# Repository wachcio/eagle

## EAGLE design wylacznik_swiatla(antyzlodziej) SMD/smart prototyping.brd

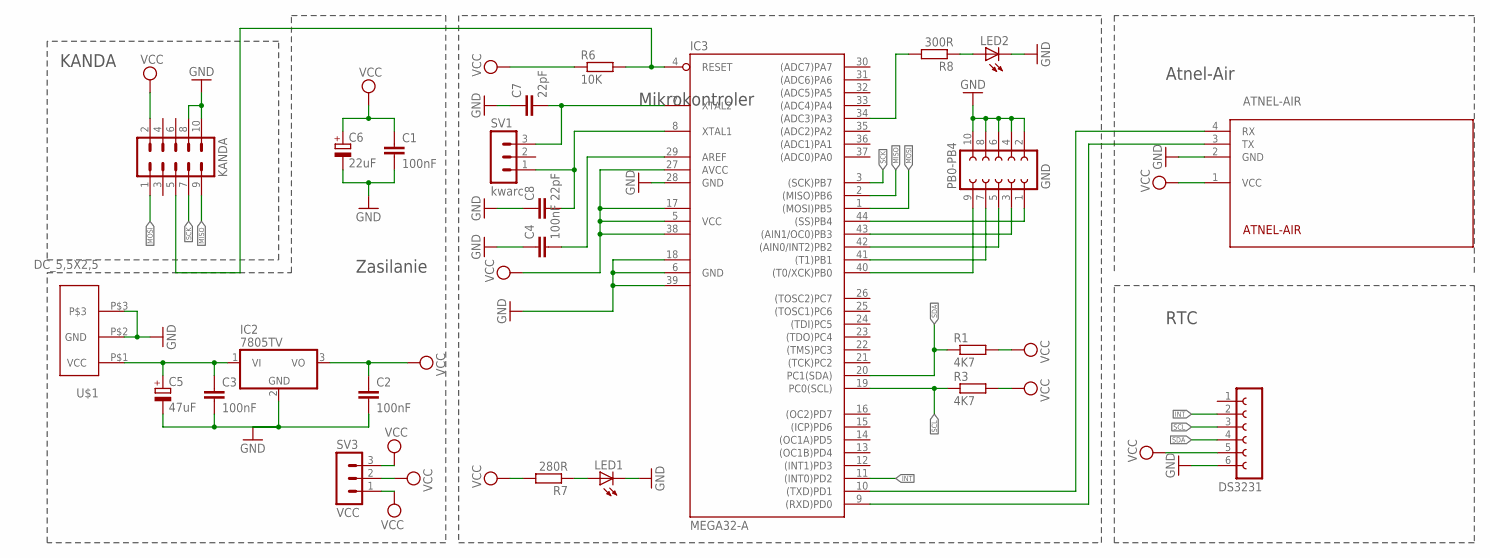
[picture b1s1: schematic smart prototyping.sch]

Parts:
ATNEL-AIR: ATNEL-AIR
C1, C2, C3, C4: 100nF; C025-024X044
C5: 47uF; B45181A
C6: 22uF; B45181A
C7, C8: 22pF; C025-024X044
DS3231: FE06-1; FE06
IC2: 7805TV; TO220V
IC3: MEGA32-A; TQFP44
KANDA: ML10
LED1, LED2: LED5MM
PB0-PB4: GND; FE05-2
R1, R3: 4K7; R1206W
R6: 10K; R1206W
R7: 280R; R1206W
R8: 300R; R1206W
SV1: kwarc; MA03-1
SV3: VCC; MA03-1
U$1: DC_5,5X2,5

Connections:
GND: ATNEL-AIR.2 (GND), C1.2, C2.2, C3.2, C4.1, C5.-, C6.-, C7.1, C8.1, DS3231.6, IC2.2 (GND), IC3.6 (GND), IC3.18 (GND1), IC3.28 (GND), IC3.39 (GND2), KANDA.8, KANDA.10, LED1.K (C), LED2.K (C), PB0-PB4.2, PB0-PB4.4, PB0-PB4.6, PB0-PB4.8, PB0-PB4.10, U$1.P$2 (GND), U$1.P$3
INT: DS3231.2, IC3.11 ((INT0)PD2)
MISO: IC3.2 ((MISO)PB6), KANDA.9
MOSI: IC3.1 ((MOSI)PB5), KANDA.1
unnamed: ATNEL-AIR.4 (RX), IC3.10 ((TXD)PD1)
unnamed: ATNEL-AIR.3 (TX), IC3.9 ((RXD)PD0)
unnamed: C4.2, IC3.29 (AREF)
unnamed: IC3.44 ((SS)PB4), PB0-PB4.1
unnamed: IC3.43 ((AIN1/OC0)PB3), PB0-PB4.3
unnamed: C3.1, C5.+, IC2.1 (VI), U$1.P$1 (VCC)
unnamed: IC3.42 ((AIN0/INT2)PB2), PB0-PB4.5
unnamed: IC3.41 ((T1)PB1), PB0-PB4.7
unnamed: IC3.40 ((T0/XCK)PB0), PB0-PB4.9
unnamed: C7.2, IC3.7 (XTAL2), SV1.3
unnamed: C8.2, IC3.8 (XTAL1), SV1.1
unnamed: LED1.A, R7.1
unnamed: LED2.A, R8.1
unnamed: IC3.34 ((ADC3)PA3), R8.2
RST: IC3.4 (RESET), KANDA.5, R6.2
SCK: IC3.3 ((SCK)PB7), KANDA.7
SCL: DS3231.3, IC3.19 (PC0(SCL)), R3.1
SDA: DS3231.4, IC3.20 (PC1(SDA)), R1.1
VCC: ATNEL-AIR.1 (VCC), C1.1, C2.1, C6.+, DS3231.5, IC2.3 (VO), IC3.5 (VCC), IC3.17 (VCC1), IC3.27 (AVCC), IC3.38 (VCC2), KANDA.2, R1.2, R3.2, R6.1, R7.2, SV3.1, SV3.2, SV3.3

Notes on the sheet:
Atnel-Air
KANDA
RTC
Zasilanie
Mikrokontroler

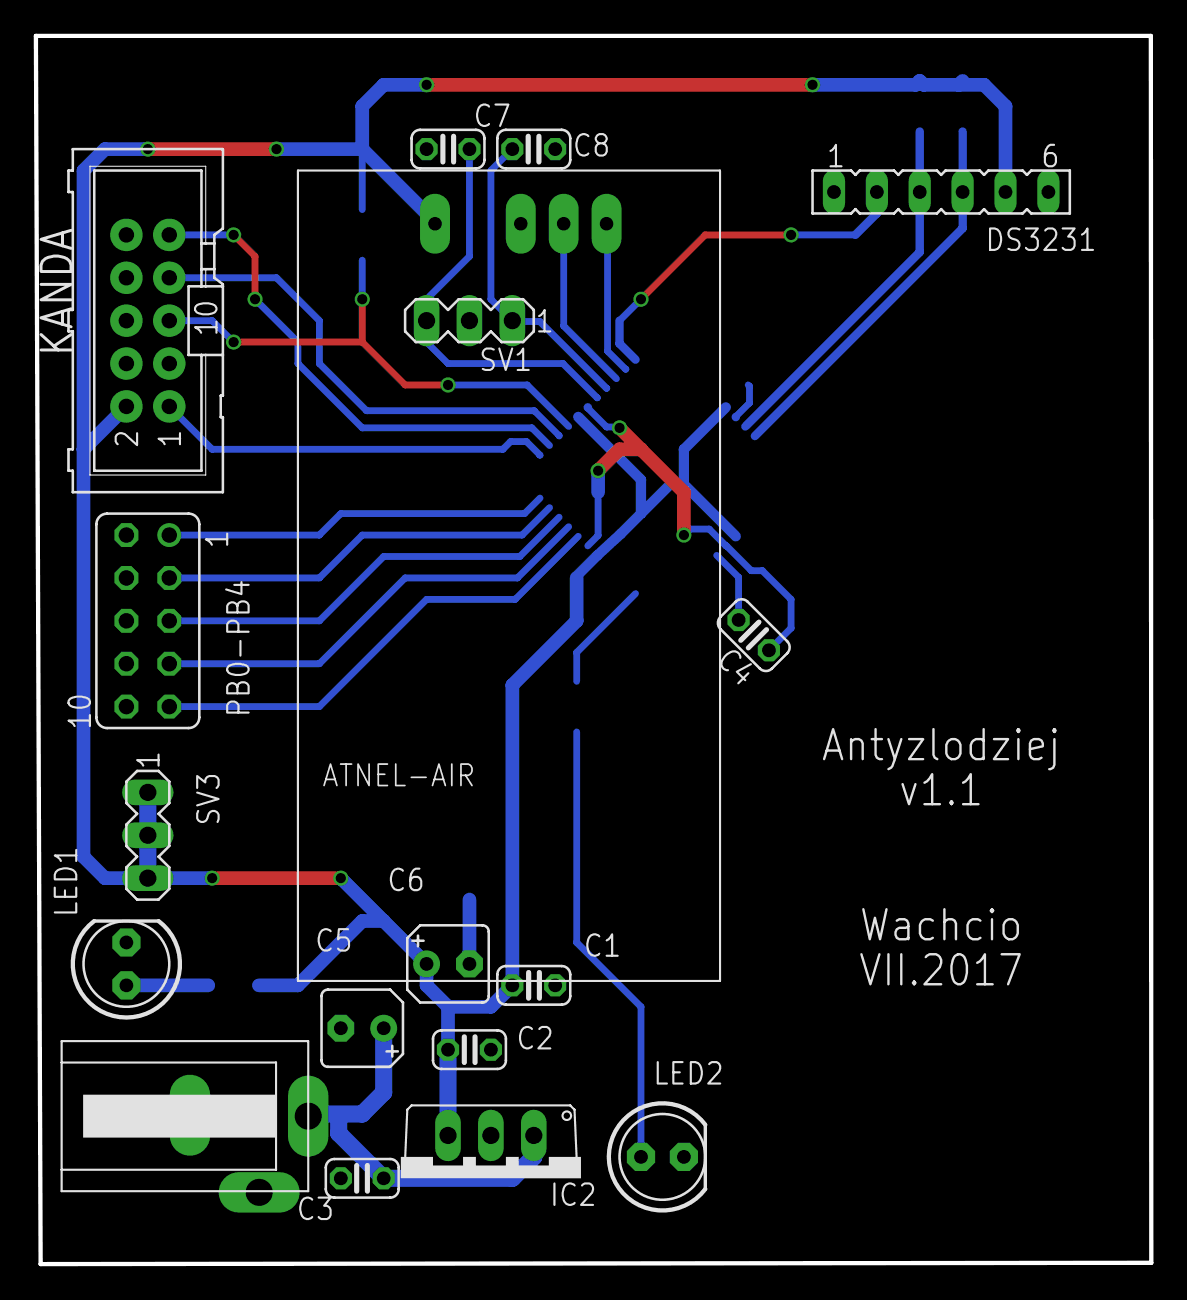
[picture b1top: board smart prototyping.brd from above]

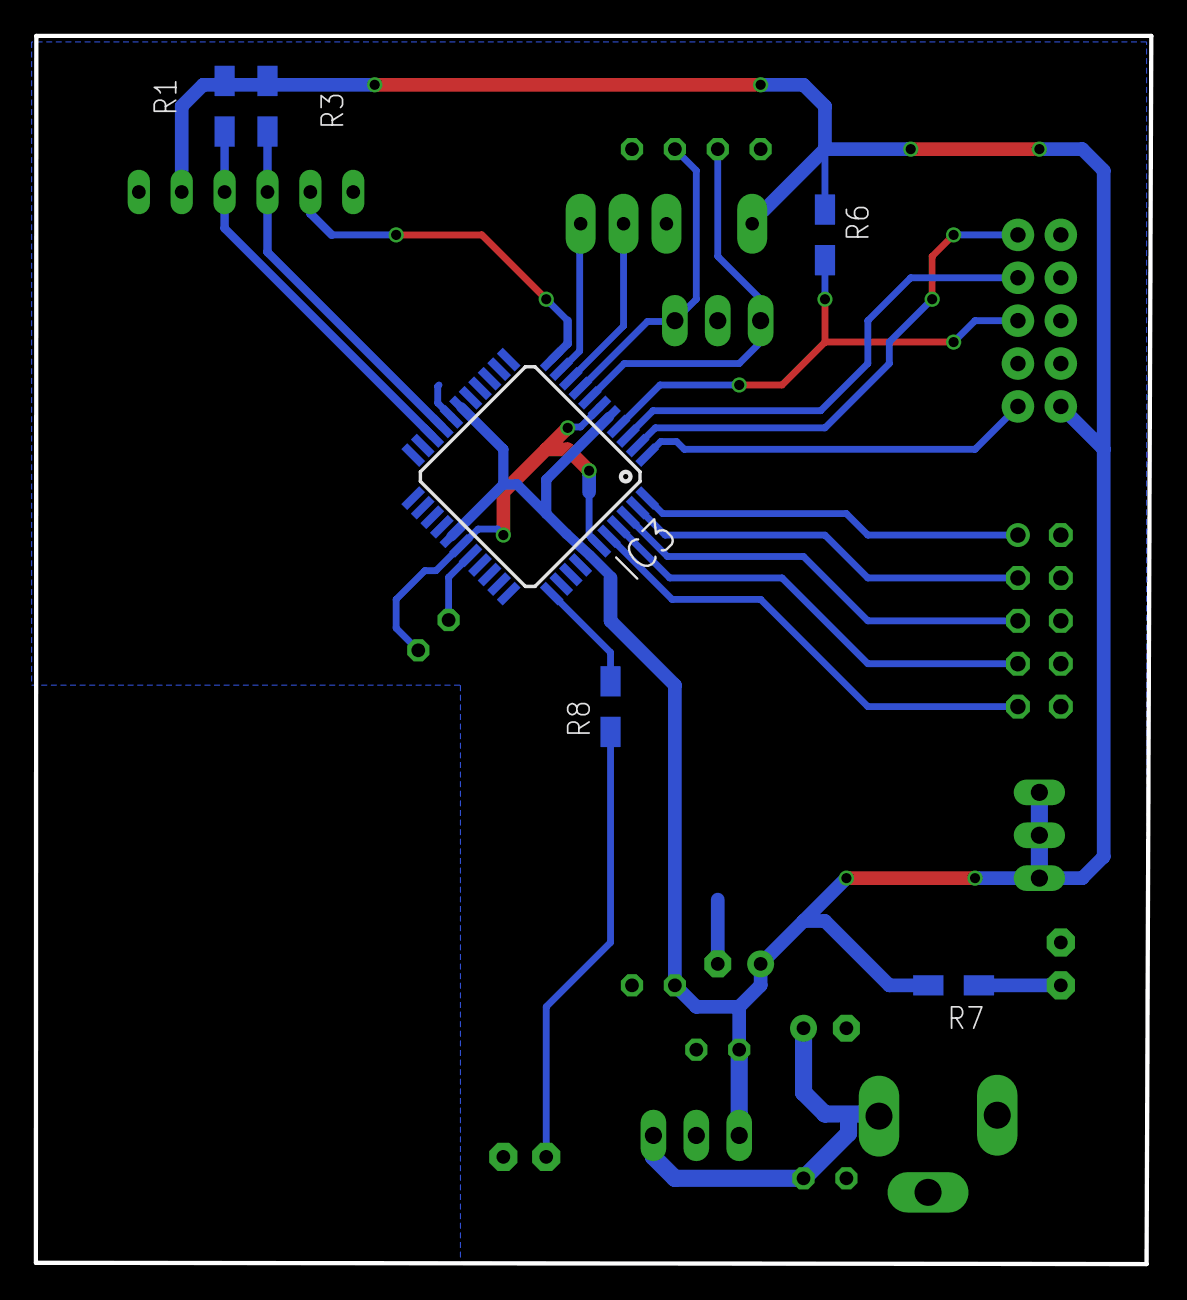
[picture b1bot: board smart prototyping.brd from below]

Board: 2 copper layers, 66.1 x 72.7 mm, 24 parts (6 on the bottom side), 23 nets.

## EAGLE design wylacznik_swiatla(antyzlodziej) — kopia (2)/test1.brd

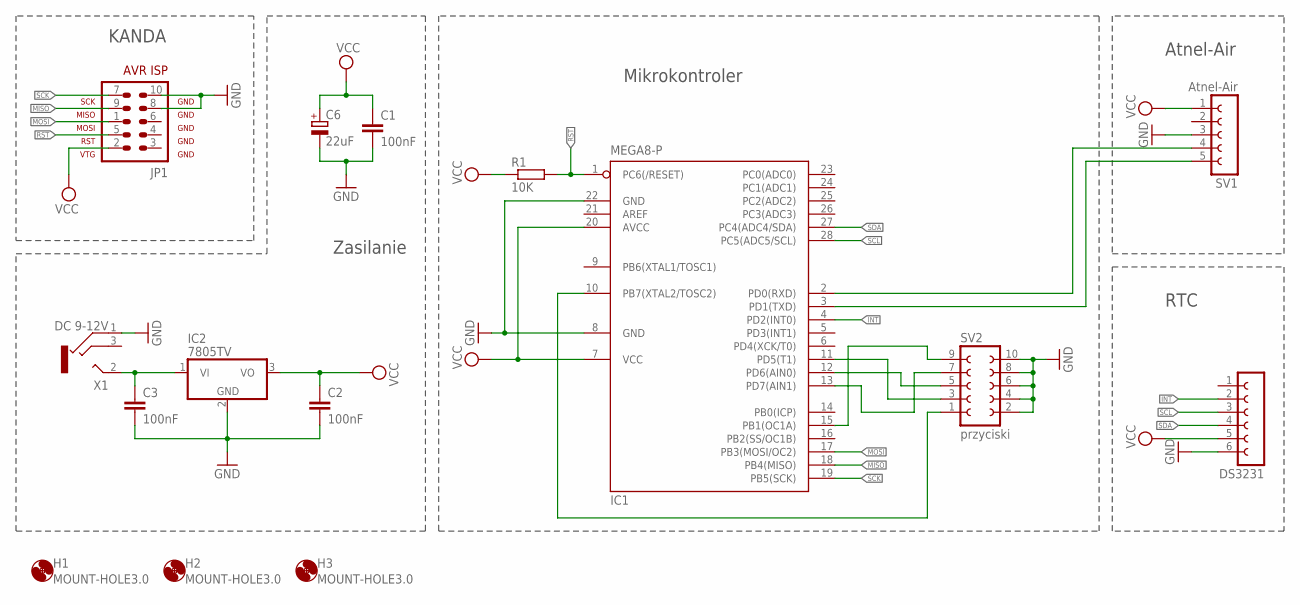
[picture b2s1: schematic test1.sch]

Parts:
C1, C2, C3: 100nF; C025-024X044
C6: 22uF; B45181A
DS3231: FE06-1; FE06
H1, H2, H3: MOUNT-HOLE3.0; 3,0
IC1: MEGA8-P; DIL28-3
IC2: 7805TV; TO220V
JP1: AVR-ISP-10
R1: 10K; 0204V
SV1: Atnel-Air; FE05-1
SV2: przyciski; FE05-2
X1: DC 9-12V; 1501_05

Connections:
GND: C1.2, C2.2, C3.2, C6.-, DS3231.6, IC1.8 (GND), IC1.22 (GND), IC2.2 (GND), JP1.8, JP1.10, SV1.3, SV2.2, SV2.4, SV2.6, SV2.8, SV2.10, X1.1
INT: DS3231.2, IC1.4 (PD2(INT0))
MISO: IC1.18 (PB4(MISO)), JP1.9
MOSI: IC1.17 (PB3(MOSI/OC2)), JP1.1
unnamed: IC1.2 (PD0(RXD)), SV1.4
unnamed: IC1.3 (PD1(TXD)), SV1.5
unnamed: IC1.10 (PB7(XTAL2/TOSC2)), SV2.1
unnamed: IC1.13 (PD7(AIN1)), SV2.7
unnamed: IC1.12 (PD6(AIN0)), SV2.5
unnamed: C3.1, IC2.1 (VI), X1.2
unnamed: IC1.15 (PB1(OC1A)), SV2.9
unnamed: IC1.11 (PD5(T1)), SV2.3
RST: IC1.1 (PC6(/RESET)), JP1.5, R1.2
SCK: IC1.19 (PB5(SCK)), JP1.7
SCL: DS3231.3, IC1.28 (PC5(ADC5/SCL))
SDA: DS3231.4, IC1.27 (PC4(ADC4/SDA))
VCC: C1.1, C2.1, C6.+, DS3231.5, IC1.7 (VCC), IC1.20 (AVCC), IC2.3 (VO), JP1.2, R1.1, SV1.1

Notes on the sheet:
Atnel-Air
KANDA
RTC
Zasilanie
Mikrokontroler

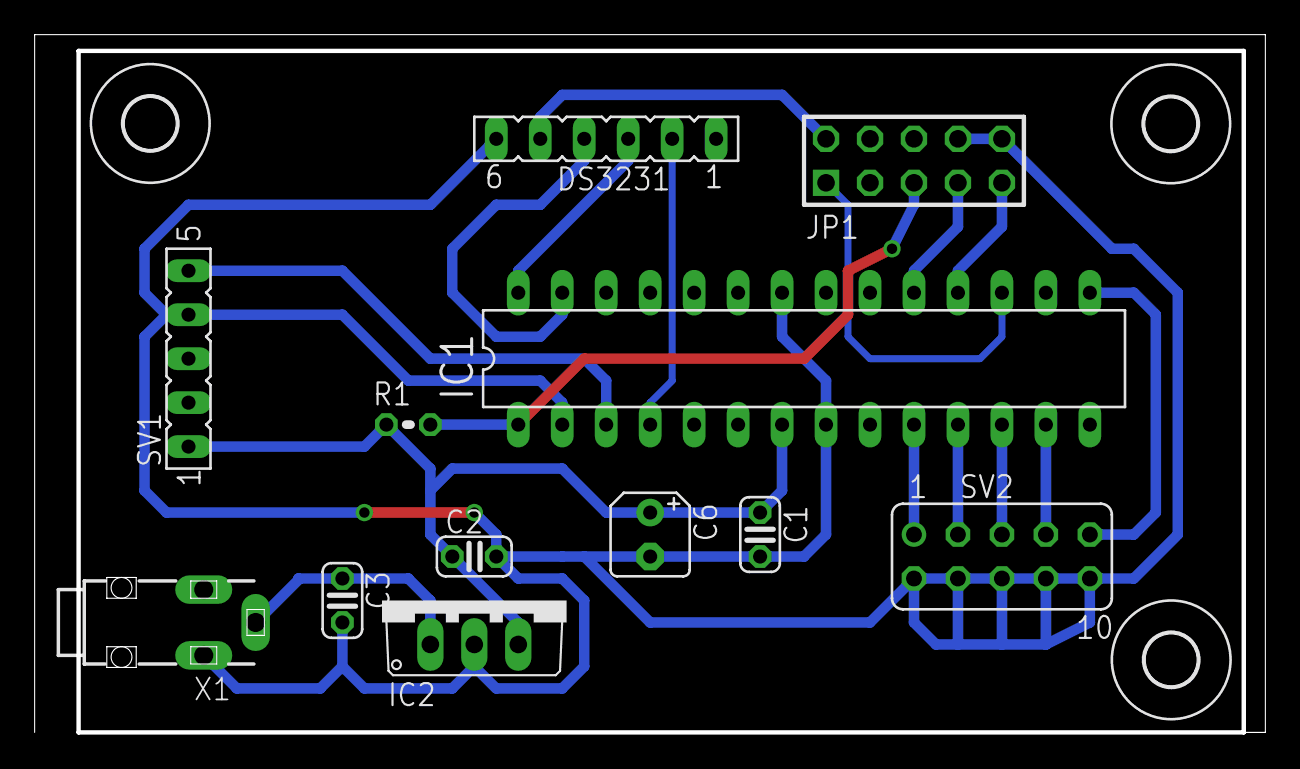
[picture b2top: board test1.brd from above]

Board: 2 copper layers, 71.1 x 40.3 mm, 15 parts (0 on the bottom side), 17 nets.
